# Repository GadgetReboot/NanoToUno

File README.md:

# NanoToUno
Arduino Nano breakout board in an Uno form factor<BR><BR>
<br><br>
Arduino KiCad symbols and footprints are from https://github.com/Alarm-Siren/arduino-kicad-library<BR><BR>

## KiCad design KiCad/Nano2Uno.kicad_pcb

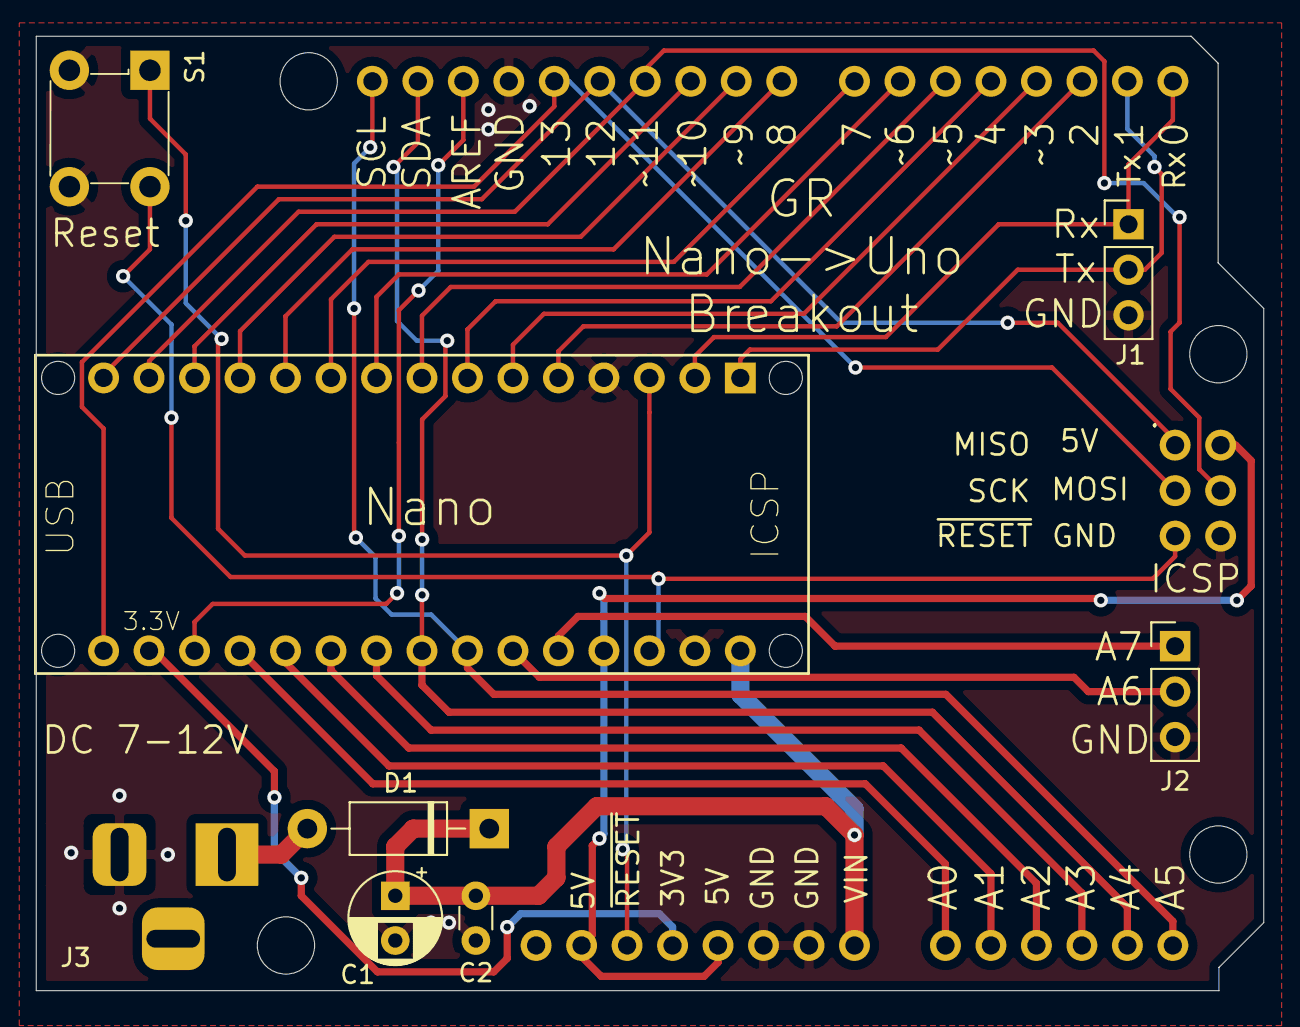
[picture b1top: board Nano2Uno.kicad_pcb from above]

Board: 2 copper layers, 68.5 x 53.3 mm, 9 parts (0 on the bottom side), 30 nets.

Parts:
C1: 4.7uF; CP_Radial_D5.0mm_P2.50mm
C2: 100nF; C_Disc_D3.0mm_W1.6mm_P2.50mm
D1: 1N5819; D_DO-41_SOD81_P10.16mm_Horizontal
J1: UART; PinHeader_1x03_P2.54mm_Vertical
J2: Analog; PinHeader_1x03_P2.54mm_Vertical
J3: PJ-102A; BarrelJack_Horizontal
M1: Arduino_Uno_Shield
M2: Arduino_Nano_Socket
S1: 1825910-6; Switch_Tactile_THT_6x6mm

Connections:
+5V: M1.5V1, M1.5V2, M1.IORF, M2.5V
GNDREF: C1.2, C2.2, J1.3, J2.3, J3.2, M1.GND1, M1.GND2, M1.GND3, M1.GND4, M2.GND1, M2.GND2, S1.3, S1.4
unnamed: C1.1, C2.1, D1.1, M1.VIN, M2.VIN
unnamed: D1.2, J3.1
unnamed: J1.1, M1.D0, M2.D0
unnamed: J1.2, M1.D1, M2.D1
unnamed: J2.1, M2.A7
unnamed: J2.2, M2.A6
unnamed: M1.3V3, M2.3V3
unnamed: M1.A0, M2.A0
unnamed: M1.A1, M2.A1
unnamed: M1.A2, M2.A2
unnamed: M1.A3, M2.A3
unnamed: M1.A4, M1.SDA, M2.A4
unnamed: M1.A5, M1.SCL, M2.A5
unnamed: M1.AREF, M2.AREF
unnamed: M1.D2, M2.D2
unnamed: M1.D3, M2.D3
unnamed: M1.D4, M2.D4
unnamed: M1.D5, M2.D5
unnamed: M1.D6, M2.D6
unnamed: M1.D7, M2.D7
unnamed: M1.D8, M2.D8
unnamed: M1.D9, M2.D9
unnamed: M1.D10, M2.D10
unnamed: M1.D11, M1.MOSI, M2.D11
unnamed: M1.D12, M1.MISO, M2.D12
unnamed: M1.D13, M1.SCK, M2.D13
unnamed: M1.RST1, M2.RST1, S1.1
unnamed: M1.RST2, M2.RST2, S1.2
